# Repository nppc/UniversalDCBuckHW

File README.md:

# UniversalDCBuckHW

A universal, digitally controlled DC-DC Buck converter with hardware design (KiCad) and high-performance AVR assembly firmware (ATtiny85).

Designed for remote digital control and telemetry via I²C from host controllers like ESP8266, ESP32, Arduino, or Raspberry Pi.

---

## Features

- **Microcontroller:** Microchip/Atmel ATtiny85 running at 8 MHz.
- **High-Frequency PWM:** 250 kHz Fast PWM using Timer1 driven by the internal 64 MHz high-speed PLL (`PLLCSR`).
- **Closed-Loop Regulation:** 1 ms loop updating PWM duty cycle to match target output voltage.
- **Configurable Slew Rate:** Smooth voltage ramping configured in (V/s) to protect connected loads against voltage spikes.
- **Dual Telemetry:** Real-time voltage ($V \times 10$) and current ($A \times 10$) sensing, with optional multi-sample moving average filtering.
- **EEPROM Storage:** Non-volatile parameter storage (voltage limits, slew rate) protected by a CRC-8 checksum.
- **I²C Slave Interface:** 7-bit addressing (`0x5E`), supporting telemetry readout and parameter configuration over standard 100 kHz bus.

---

## Repository Structure

```
UniversalDCBuckHW/
├── Firmware/
│   └── Assembler/
│       └── UDCBuckHW/          # ATtiny85 assembly source code
│           ├── main.asm        # Entry point, vector table, main loop
│           ├── I2C.inc         # USI-based I2C slave state machine
│           ├── PWM.inc         # Timer1 64 MHz PLL & 250 kHz PWM setup
│           ├── ADC.inc         # ADC channel sequencing & conversion
│           ├── scheduler.inc   # Timer0 1 ms rate scheduler & voltage ramps
│           ├── EEPROM.inc      # EEPROM read/write with CRC-8 validation
│           ├── MovAverage.inc  # Running moving-average filter
│           ├── math.inc        # 16-bit unsigned division routine
│           └── main.inc        # Buffer sync, PWM regulation, unit conversions
├── KiCad/                      # KiCad schematics and PCB layout
│   ├── UniDCBuckHW.sch         # Main converter schematic (IR2101S, MOSFETs, etc.)
│   ├── UniDCBuckHW.kicad_pcb   # PCB board layout
│   └── Adapter1-25to1/         # Adapter board files
├── SCAD/                       # OpenSCAD 3D models for power components
├── Refs/                       # Component datasheets & reference materials
└── bin/                        # Pre-built binaries (.hex) and flashing scripts
```

---

## Hardware Architecture

### Pinout (ATtiny85)

| Pin | Name | Direction | Description |
| :---: | :--- | :---: | :--- |
| **PB0** | `PIN_SDA` | I/O | I²C Serial Data (USI Two-Wire) |
| **PB1** | `PIN_PWM` | Output | 250 kHz PWM signal to MOSFET driver (`OC1A`) |
| **PB2** | `PIN_SCL` | Input | I²C Serial Clock (USI Two-Wire) |
| **PB3** | `PIN_Isense` | Input | ADC3 current measurement (e.g. 185 mV/A sensor) |
| **PB4** | `PIN_Vsense` | Input | ADC2 voltage divider feedback |
| **PB5** | `RESET` | Input | Active-low reset (ISP programming) |

### Power Stage
- **Gate Driver:** IR2101S high-and-low side MOSFET driver.
- **Power Switches:** IRLR8726PbF N-channel power MOSFETs (DPAK).
- **Freewheeling Diode:** PPS1045 Schottky barrier rectifier.
- **Inductor:** PCV-2-473-10L high-current power inductor.

---

## I²C Protocol & Memory Map

- **Slave Address:** `0x5E` (7-bit), `0xBC` (8-bit write), `0xBD` (8-bit read)
- **Bus Speed:** 100 kHz Standard Mode (recommended)

### Buffer Layout (11 Bytes)

| Offset | Field | Access | Format / Units | Description |
| :---: | :--- | :---: | :---: | :--- |
| `0` | `Voltage_Set` | R/W | $V \times 10$ (e.g., $120 = 12.0\text{ V}$) | Target output voltage. Set to `0` to turn off output. |
| `1` | `Voltage_Change` | R/W | $(V \times 10) / \text{s}$ (e.g., $10 = 1.0\text{ V/s}$) | Slew rate limit ($\ge 4$). |
| `2` | `Voltage_Min` | R/W | $V \times 10$ (e.g., $10 = 1.0\text{ V}$) | Minimum allowed output voltage. |
| `3` | `Voltage_Max` | R/W | $V \times 10$ (e.g., $120 = 12.0\text{ V}$) | Maximum allowed output voltage. |
| `4` | `PWM_Value` | R | $0 - 255$ | Current PWM duty cycle (`OCR1A`). |
| `5` | `Voltage_Measured` | R | $V \times 10$ | Measured output voltage. |
| `6` | `Current_Measured` | R | $A \times 10$ (e.g., $25 = 2.5\text{ A}$) | Measured output current. |
| `7` | `Voltage_RAW_L` | R | Low byte | 10-bit raw ADC reading for voltage. |
| `8` | `Voltage_RAW_H` | R | High byte | 10-bit raw ADC reading for voltage. |
| `9` | `Current_RAW_L` | R | Low byte | 10-bit raw ADC reading for current. |
| `10` | `Current_RAW_H` | R | High byte | 10-bit raw ADC reading for current. |

---

## Communication Examples

### Arduino / ESP8266 / ESP32 (C++ `Wire.h`)

#### Setting Output Voltage and Limits (Write)
```cpp
#include <Wire.h>

#define BUCK_I2C_ADDR 0x5E

void setBuckVoltage(float targetVolts, float slewRateVPerSec, float minVolts, float maxVolts) {
    uint8_t vSet   = (uint8_t)(targetVolts * 10.0f);     // e.g. 12.0V -> 120
    uint8_t vChg   = (uint8_t)(slewRateVPerSec * 10.0f); // e.g. 1.0V/s -> 10 (min 4)
    uint8_t vMin   = (uint8_t)(minVolts * 10.0f);        // e.g. 3.3V -> 33
    uint8_t vMax   = (uint8_t)(maxVolts * 10.0f);        // e.g. 15.0V -> 150

    Wire.beginTransmission(BUCK_I2C_ADDR);
    Wire.write(vSet);
    Wire.write(vChg);
    Wire.write(vMin);
    Wire.write(vMax);
    Wire.endTransmission();
}

void turnOffBuck() {
    // Setting Voltage_Set = 0 immediately disables PWM regulation
    Wire.beginTransmission(BUCK_I2C_ADDR);
    Wire.write(0);
    Wire.endTransmission();
}
```

#### Reading Telemetry (Read)
```cpp
#include <Wire.h>

#define BUCK_I2C_ADDR 0x5E

struct BuckTelemetry {
    float voltageSet;
    float voltageChange;
    float voltageMin;
    float voltageMax;
    uint8_t pwmDuty;
    float voltageMeasured;
    float currentMeasured;
    uint16_t adcRawVoltage;
    uint16_t adcRawCurrent;
};

bool readBuckTelemetry(BuckTelemetry &data) {
    uint8_t bytesReceived = Wire.requestFrom(BUCK_I2C_ADDR, 11);
    if (bytesReceived < 11) {
        return false; // Incomplete read or slave not responding
    }

    uint8_t buf[11];
    for (int i = 0; i < 11; i++) {
        buf[i] = Wire.read();
    }

    data.voltageSet       = buf[0] / 10.0f;
    data.voltageChange    = buf[1] / 10.0f;
    data.voltageMin       = buf[2] / 10.0f;
    data.voltageMax       = buf[3] / 10.0f;
    data.pwmDuty          = buf[4];
    data.voltageMeasured  = buf[5] / 10.0f;
    data.currentMeasured  = buf[6] / 10.0f;
    data.adcRawVoltage    = buf[7] | ((uint16_t)buf[8] << 8);
    data.adcRawCurrent    = buf[9] | ((uint16_t)buf[10] << 8);

    return true;
}
```

---

### Python (Raspberry Pi / `smbus2`)

```python
from smbus2 import SMBus, i2c_msg
import time

I2C_BUS = 1
BUCK_ADDR = 0x5E

def set_voltage(bus, target_v, slew_rate=1.0, min_v=3.3, max_v=15.0):
    v_set = int(target_v * 10)
    v_chg = max(4, int(slew_rate * 10))
    v_min = int(min_v * 10)
    v_max = int(max_v * 10)
    
    msg = i2c_msg.write(BUCK_ADDR, [v_set, v_chg, v_min, v_max])
    bus.i2c_rdwr(msg)

def read_telemetry(bus):
    msg = i2c_msg.read(BUCK_ADDR, 11)
    bus.i2c_rdwr(msg)
    data = list(msg)
    
    return {
        "v_set": data[0] / 10.0,
        "v_change": data[1] / 10.0,
        "v_min": data[2] / 10.0,
        "v_max": data[3] / 10.0,
        "pwm_duty": data[4],
        "v_measured": data[5] / 10.0,
        "current_a": data[6] / 10.0,
        "raw_v_adc": data[7] | (data[8] << 8),
        "raw_i_adc": data[9] | (data[10] << 8)
    }

with SMBus(I2C_BUS) as bus:
    # Set to 12.0V output
    set_voltage(bus, target_v=12.0, slew_rate=1.0, min_v=3.3, max_v=15.0)
    time.sleep(0.5)
    
    # Read telemetry
    telemetry = read_telemetry(bus)
    print(f"Output: {telemetry['v_measured']:.1f} V, Current: {telemetry['current_a']:.1f} A, PWM: {telemetry['pwm_duty']}/255")
```

---

## Building and Flashing

### Building Firmware

#### Option 1: CMake & Ninja (MPLAB / VS Code)
```powershell
cmake --build "Firmware/Assembler/UDCBuckHW/_build/HWBuckAtTiny85/default" --clean-first
```

#### Option 2: AVRASM2 Command Line
```powershell
avrasm2.exe -o bin/UDCBuckHW.hex -fI Firmware/Assembler/UDCBuckHW/main.asm
```

### Flashing with USBasp & AVRDUDE

Run `bin/flash.cmd` or invoke `avrdude` directly:
```bash
avrdude -c usbasp -p t85 -U flash:w:bin/UDCBuckHW.hex:i
```

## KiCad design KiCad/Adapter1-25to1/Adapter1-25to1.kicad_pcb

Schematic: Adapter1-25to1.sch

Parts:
J1: Conn_01x06_Male; Pads_prog_6pin1.25mm
J2: Conn_01x06; JST_SH_6x1mm
J3: Conn_01x06_Male; Pin_Header_Angled_1x06_Pitch1.27mm

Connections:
unnamed: J1.1, J2.1, J3.1
unnamed: J1.2, J2.2, J3.2
unnamed: J1.3, J2.3, J3.3
unnamed: J1.4, J2.4, J3.4
unnamed: J1.5, J2.5, J3.5
unnamed: J1.6, J2.6, J3.6

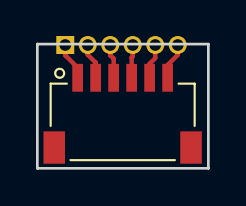
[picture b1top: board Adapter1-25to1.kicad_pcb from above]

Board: 2 copper layers, 9.5 x 6.9 mm, 3 parts (1 on the bottom side), 6 nets.

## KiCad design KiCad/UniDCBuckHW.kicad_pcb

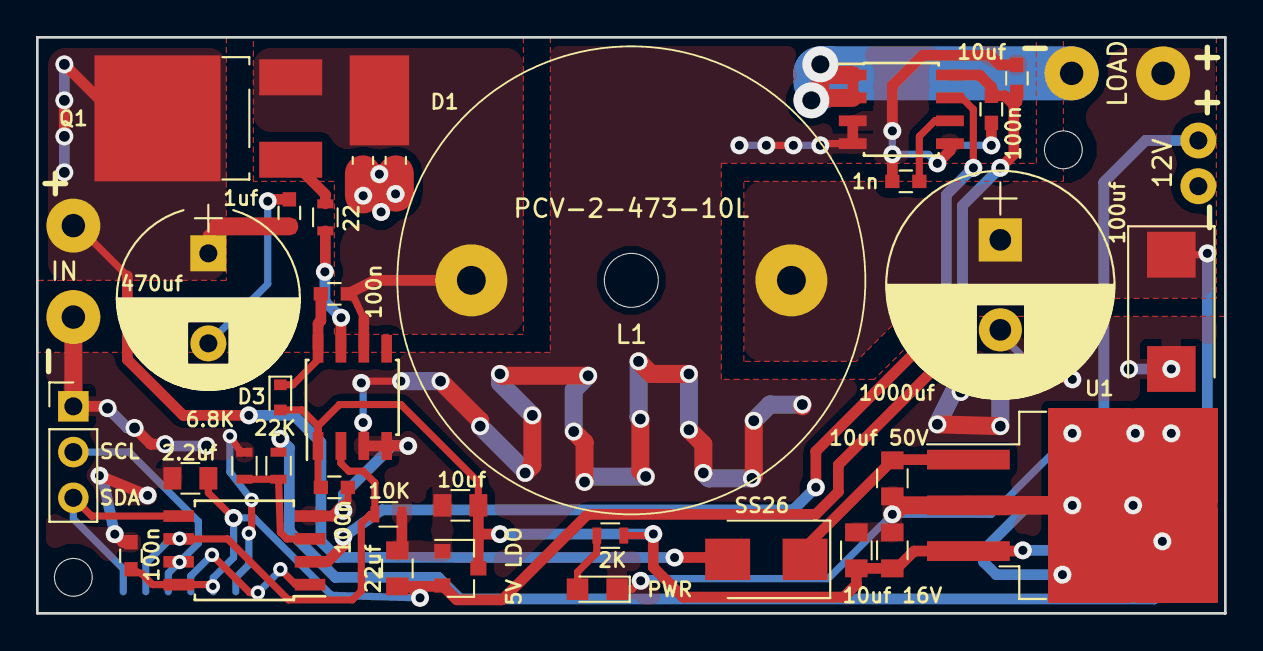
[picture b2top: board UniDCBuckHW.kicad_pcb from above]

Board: 2 copper layers, 66.0 x 32.0 mm, 37 parts (1 on the bottom side), 19 nets.

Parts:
C1: 10uf 50V; C_0805
C2: 10uf; C_0805
C3, C5: 10uf 16V; C_0805
C4: 2.2uf; C_0805
C6: 470uf; CP_Radial_D10.0mm_P5.00mm
C7, C8, C11, C14: 100n; C_0603
C9: 1uf; C_0603
C10: 1000uf; CP_Radial_D12.5mm_P5.00mm
C12: 100uf; CP_Tantalum_Case-V_EIA-7343-20_Reflow
C13: 22uf; C_0805
C15: 1n; C_0603
C16: 10uf; C_0603
D1: PPS1045; D_Powermite3
D2: SS26; D_SMB
D3: 1N5819; D_SOD-523
D4: LED; LED_0805
J1: IN; Conn_Power
J2: 12V; Conn2pin_2.54mm
J3: i2c; Pin_Header_Straight_1x03_Pitch2.54mm
J4: LOAD; Conn_Power
J5: PROG; Pads_prog_6pin1.25mm
L1: 47uH; PCV-2-473-10L
Q1: IRLR8726PBF; TO-252-2_Rectifier
R1: 22K; R_0603
R2: 6.8K; R_0603
R3: 10K; R_0603
R4: 22; R_0603
R5: 2K; R_0603
U1: LM2940-12V; TO-263-3_TabPin2
U2: MCP1703-5V; SOT-23
U3: IR2101; SOIC-8_3.9x4.9mm_Pitch1.27mm
U4: ATTINY85-20SU; SOIJ-8_5.3x5.3mm_Pitch1.27mm
U5: ACS712-5; SOIC-8_3.9x4.9mm_Pitch1.27mm

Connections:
+5V: C4.2, C11.2, C13.2, C14.2, C16.2, J5.5, U2.2, U4.8, U5.8
+12V: C2.2, C3.2, C5.2, C7.2, D3.2, J2.2, R5.2, U1.3, U2.3, U3.1
/Isense: U4.2, U5.7
/PWM: J5.2, R3.2, U3.2, U4.6
/RST: J5.4, U4.1
/SCL: J3.2, J5.3, U4.7
/SDA: J3.3, J5.1, U4.5
/VOUT: C10.1, C12.1, J4.1, L1.2, R1.2
/Vsense: R1.1, R2.2, U4.3
GND: C1.1, C2.1, C3.1, C4.1, C5.1, C6.2, C7.1, C9.1, C10.2, C11.1, C12.2, C13.1, C14.1, C15.1, C16.1, D1.2, D4.1, J1.1, J2.1, J3.1, J5.6, R2.1, R3.1, U1.2, U2.1, U3.3, U3.4, U4.4, U5.3, U5.4, U5.5
unnamed: C1.2, D2.1, U1.1
unnamed: C6.1, C9.2, D2.2, J1.2, Q1.2
unnamed: C8.1, D1.1, L1.1, Q1.3, U3.6
unnamed: C8.2, D3.1, U3.8
unnamed: C15.2, U5.6
unnamed: D4.2, R5.1
unnamed: J4.2, U5.1, U5.2
unnamed: Q1.1, R4.1
unnamed: R4.2, U3.7

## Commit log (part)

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2018-08-02 3d part
2018-08-03 Refs added. Initial KiCad
2018-08-05 Draft PCB is ready
2018-08-05 Final Vq PCB
2018-08-07 minor changes
2018-08-13 Started to write I2C routines
2018-08-22 test i2c addr
2018-08-23 debug i2c
2018-08-23 i2c 90% completed
2018-08-24 Adjust gitignore
2018-08-24 still issues with i2c
2018-08-26 ADC and PWM routines started
2018-08-27 I2C working for receiving data
2018-08-28 I2C draft for sending data. Not tested
2018-08-28 I2C read/write working
2018-08-29 Added EEPROM and Scheduler routines
2018-08-30 I2C exchange routines are finished
2018-08-30 Some progress on converting ADC values
2018-08-31 Firmware is completed, but not tested.
2018-09-02 Needed to move ADC from interrupts to main code. Othervise I2C works unstable
2018-09-02 Cleanup and I reading error fix
2018-09-03 Check for max voltage
2018-09-04 Change SRAM variable to register. Performance in interrupt inmproved
2020-04-30 47/10 divider
